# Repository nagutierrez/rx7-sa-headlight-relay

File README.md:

# RX-7 SA Headlight Relay Board

A replacement headlight assembly relay board for the 1979-1980 Mazda RX-7.

## Context

The first generation Mazda RX-7 SA (79-80) features a self-contained pop-up headlight assembly. This assembly contains the sensor and relay necessary to correctly position itself in the up or down position dependent on signal.

After decades of operation the relay in this assembly may fail, causing the headlight to no longer go up and down, or do so intermittently. While this relay could be replaced with a generic automotive relay, some functionality could be lost as it includes an additional diode protected output for the dashboard headlight indicator.

This project defines a replacement board with modern easily sourcable parts that maintains original functionality with no modifications necessary to wiring and no visible changes.

## Prerequisit Reading

Please understand the RX-7 wiring diagram before attempting any electrical work!

Original Source: http://www.wright-here.net/files/manuals/1979RX7WiringDiagram.pdf

Archive for posterity: https://archive.org/details/1979-rx-7-wiring-diagram

## Sections

- [Teardown](./documentation/00-teardown.md)
- [Design](./documentation/01-design.md)
- [Parts](./documentation/02-parts.md)
- [Construction](./documentation/03-construction.md)

## Directory Structure

- `documentation` - documentation for the project
- `hardware` - KiCad hardware design files
- `production` - production files for the PCB (zip this up and send it to your favorite PCB manufacturer)

## Caveats

- I suspect this will work with the FB RX-7 but cannot verify since the headlight assembly appears to be slightly different
- This was my first PCB project
- Please understand what you are doing; I bear no responsibility for any damage you may cause to yourself or your vehicle
- Manufacturing of the board is not included in the scope of this project; there are plenty of low cost pcb manufacturers that can guide you through the process

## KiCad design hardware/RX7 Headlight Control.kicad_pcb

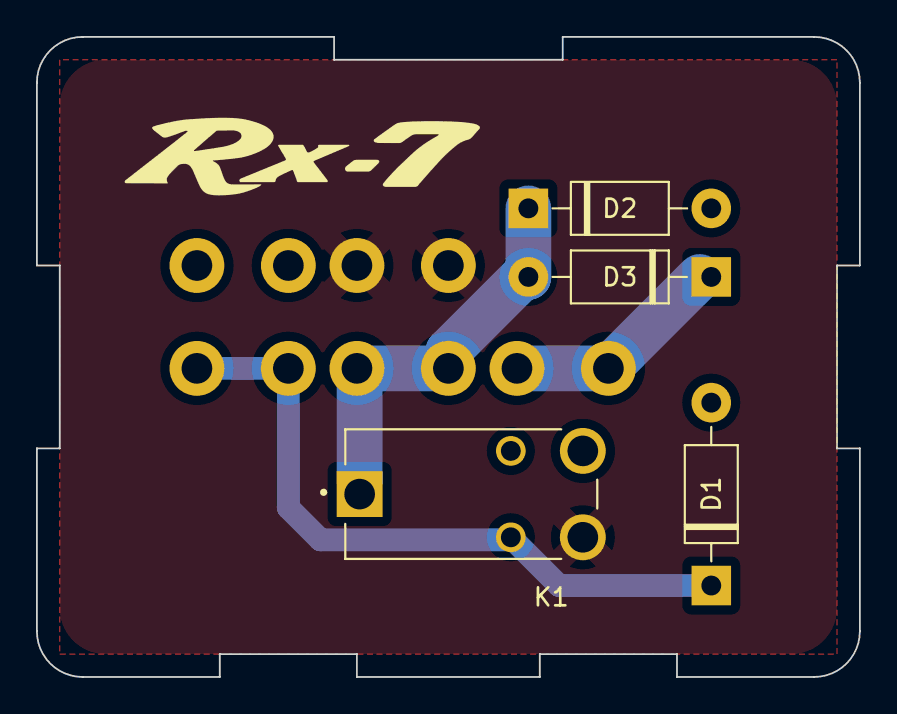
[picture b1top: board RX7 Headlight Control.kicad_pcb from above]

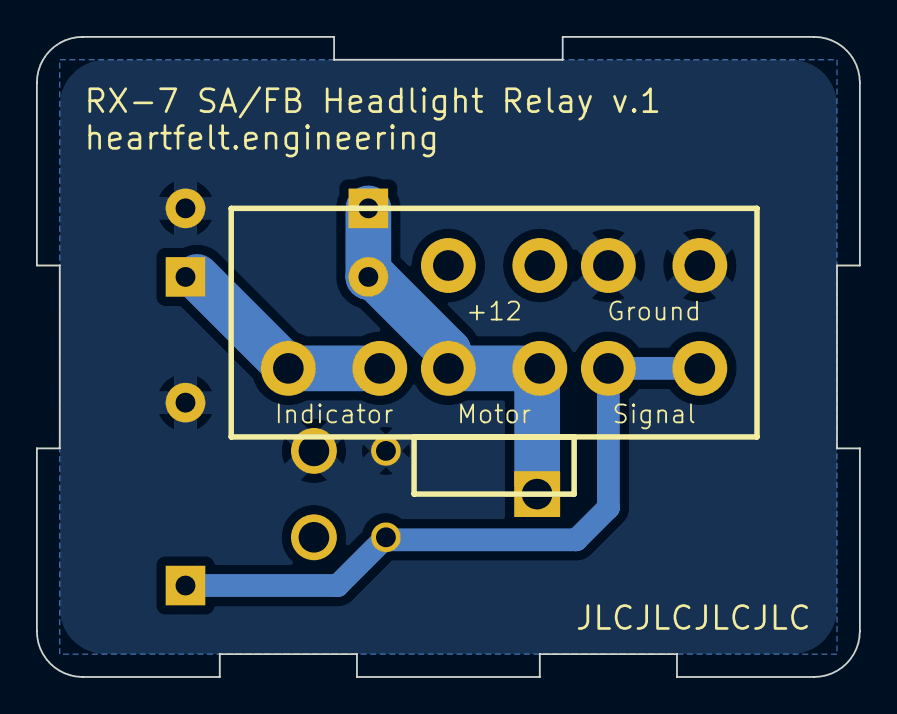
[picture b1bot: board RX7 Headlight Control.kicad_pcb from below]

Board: 2 copper layers, 45.7 x 35.6 mm, 9 parts (5 on the bottom side), 5 nets.

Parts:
+12: +12; Molex_197054001
D1, D2, D3: 1N5819; D_DO-41_SOD81_P10.16mm_Horizontal
Ground: Ground; Molex_197054001
Indicator: Ind; Molex_197054001
K1: G8N-1L-DC12; RELAY_G8N-1L-DC12
Motor: Motor; Molex_197054001
Signal: Signal; Molex_197054001

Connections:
+12: +12.1, K1.3
Ground: D1.2 (A), D2.2 (A), Ground.1, K1.4, K1.5
Indicator: D3.1 (K), Indicator.1
Output: D2.1 (K), D3.2 (A), K1.1, Motor.1
Signal: D1.1 (K), K1.2, Signal.1

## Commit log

2023-03-18 Initial creation of repo
